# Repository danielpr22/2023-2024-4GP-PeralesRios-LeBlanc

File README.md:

# 2023-2024-4gp-name_a-name_b

TD Capteur : Name A - Name B

## TODO List

- [x] Create repository on MOSH-Insa-Toulouse organization
- [x] Add KiCad project with version 7.0.10
- [x] Create KiCad schematic
- [x] Add Arduino project

## KiCad project

Shield Arduino...

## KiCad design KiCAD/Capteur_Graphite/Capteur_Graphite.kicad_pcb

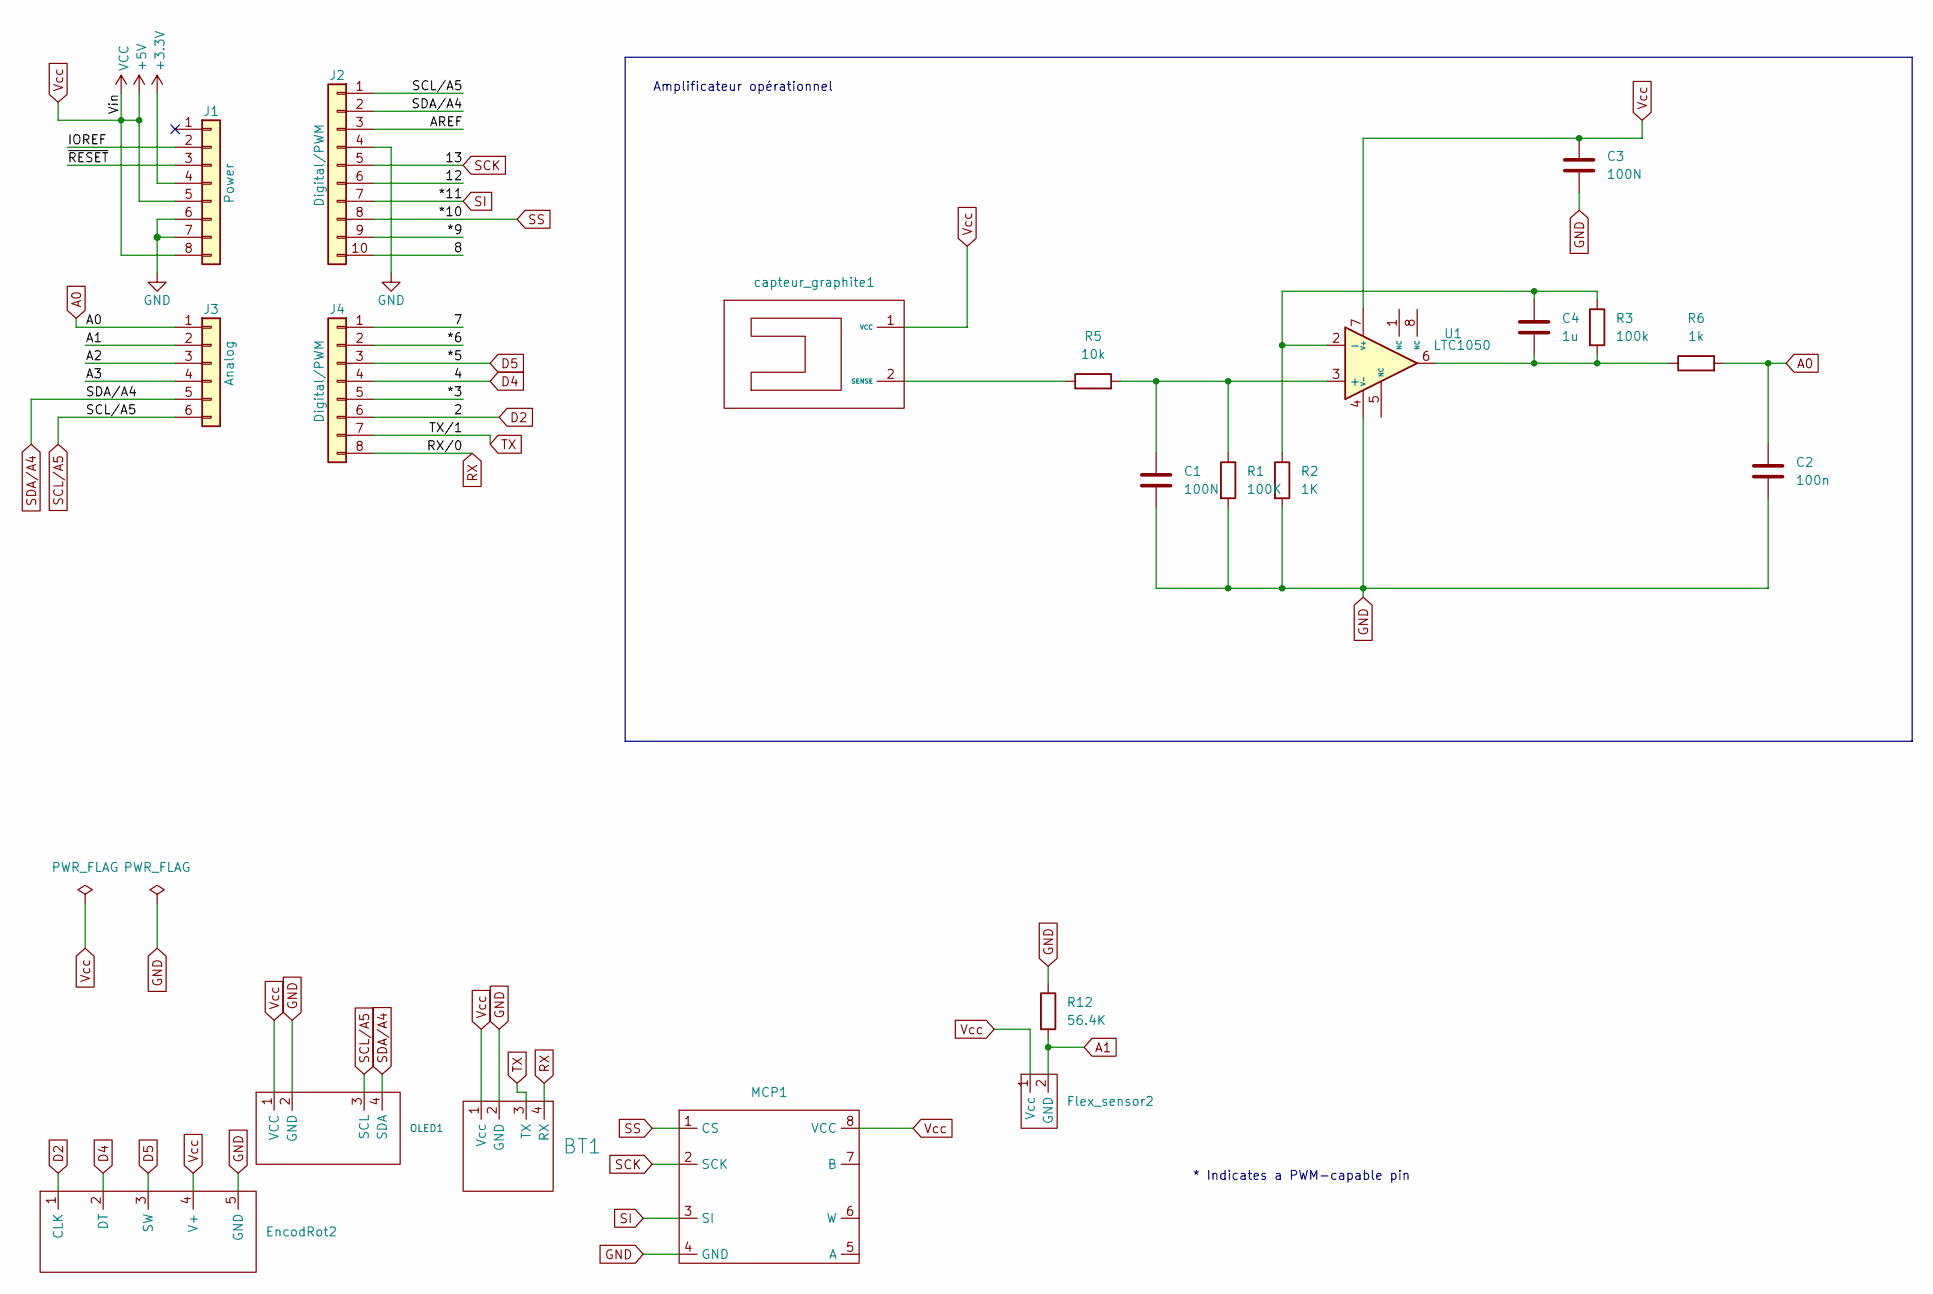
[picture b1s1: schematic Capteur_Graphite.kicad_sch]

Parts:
BT1: Bluetooth
C1, C3: 100N; C_Radial_D5.0mm_H5.0mm_P2.00mm
C2: 100n; C_Radial_D5.0mm_H5.0mm_P2.00mm
C4: 1u; C_Radial_D5.0mm_H5.0mm_P2.00mm
EncodRot2: Encodeur
Flex_sensor2: FLEX
J1: Power; PinSocket_1x08_P2.54mm_Vertical
J2: Digital/PWM; PinSocket_1x10_P2.54mm_Vertical
J3: Analog; PinSocket_1x06_P2.54mm_Vertical
J4: Digital/PWM; PinSocket_1x08_P2.54mm_Vertical
MCP1: MCP41050
OLED1: OLED
R1: 100K; R_Axial_DIN0204_L3.6mm_D1.6mm_P1.90mm_Vertical
R2: 1K; R_Axial_DIN0204_L3.6mm_D1.6mm_P1.90mm_Vertical
R3: 100k; R_Axial_DIN0204_L3.6mm_D1.6mm_P1.90mm_Vertical
R5: 10k; R_Axial_DIN0204_L3.6mm_D1.6mm_P1.90mm_Vertical
R6: 1k; R_Axial_DIN0204_L3.6mm_D1.6mm_P1.90mm_Vertical
R12: 56.4K; R_Axial_DIN0204_L3.6mm_D1.6mm_P1.90mm_Vertical
U1: LTC1050
capteur_graphite1: Capteur_graphite

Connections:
+3V3: J1.4
/7: J4.1
/8: J2.10
/12: J2.6
/*3: J4.5
/*6: J4.2
/*9: J2.9
/A2: J3.3
/A3: J3.4
/AREF: J2.3
/IOREF: J1.2
/~RESET: J1.3
A0: C2.2, J3.1, R6.2
A1: Flex_sensor2.2 (GND), J3.2, R12.2
D2: EncodRot2.1 (CLK), J4.6
D4: EncodRot2.2 (DT), J4.4
D5: EncodRot2.3 (SW), J4.3
GND: BT1.2 (GND), C1.2, C2.1, C3.2, EncodRot2.5 (GND), J1.6, J1.7, J2.4, MCP1.4 (GND), OLED1.2 (GND), R1.2, R2.2, R12.1, U1.4 (V-)
unnamed: C4.2, R3.2, R6.1, U1.6
unnamed: C1.1, R1.1, R5.2, U1.3 (+)
unnamed: C4.1, R2.1, R3.1, U1.2 (-)
unnamed: R5.1, capteur_graphite1.2 (SENSE)
RX: BT1.4 (RX), J4.8
SCK: J2.5, MCP1.2 (SCK)
SCL/A5: J2.1, J3.6, OLED1.3 (SCL)
SDA/A4: J2.2, J3.5, OLED1.4 (SDA)
SI: J2.7, MCP1.3 (SI)
SS: J2.8, MCP1.1 (CS)
TX: BT1.3 (TX), J4.7
Vcc: BT1.1 (Vcc), C3.1, EncodRot2.4 (V+), Flex_sensor2.1 (Vcc), J1.5, J1.8, MCP1.8 (VCC), OLED1.1 (VCC), U1.7 (V+), capteur_graphite1.1 (VCC)

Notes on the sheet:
* Indicates a PWM-capable pin
Amplificateur opérationnel

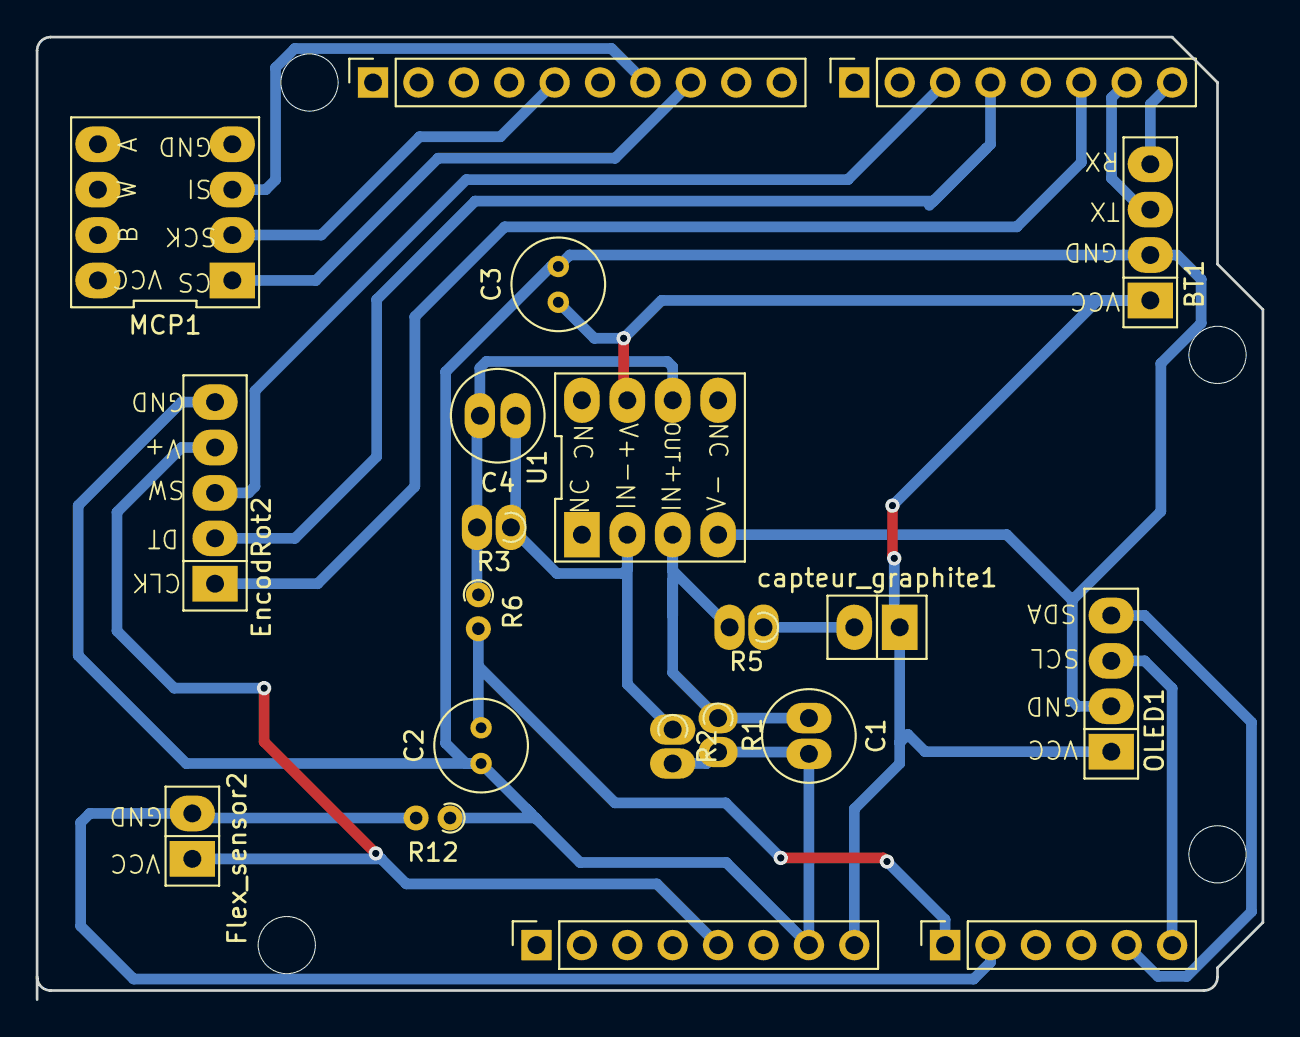
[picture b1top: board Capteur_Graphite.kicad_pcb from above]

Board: 2 copper layers, 68.6 x 53.8 mm, 25 parts (0 on the bottom side), 18 nets.

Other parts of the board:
MH1, MH2, MH3, MH4: MountingHole_3.2mm

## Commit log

2024-02-14 Add README TODO list
2024-02-14 Update KiCad version
2024-02-14 Add KiCad file
2024-02-14 Create KiCad schematic
2024-02-14 Add Arduino project
2024-03-17 Create Test_Bluetooth.ino
    BT
